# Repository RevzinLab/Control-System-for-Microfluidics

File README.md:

# Control-System-for-Microfluidics

The files included in this repository were developed by The Revzin Lab.

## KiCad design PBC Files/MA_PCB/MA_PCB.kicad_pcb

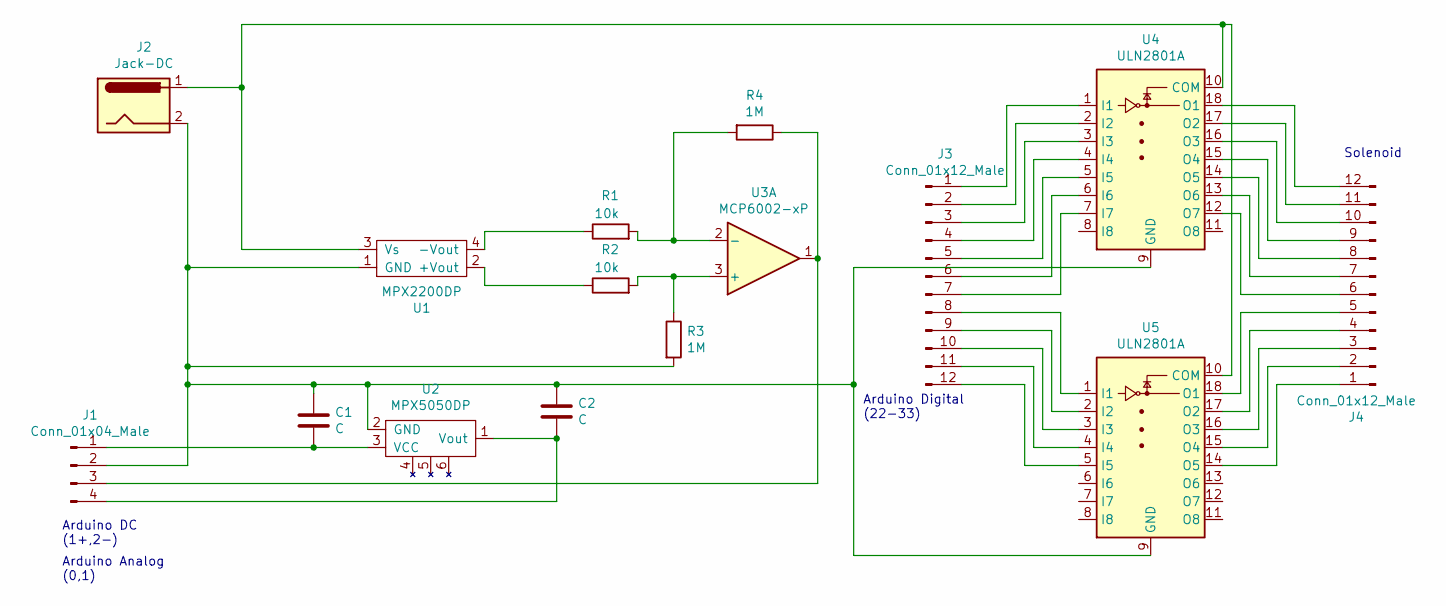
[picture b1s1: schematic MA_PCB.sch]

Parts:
C1, C2: C; CP_Radial_Tantal_D4.5mm_P5.00mm
J1: Conn_01x04_Male; TerminalBlock_4Ucon_1x04_P3.50mm_Vertical
J2: Jack-DC; MI-179PH
J3: Conn_01x12_Male; IDC-Header_2x06-1MP_P2.54mm_Latch6.5mm_Vertical
J4: Conn_01x12_Male; TerminalBlock_4Ucon_1x12_P3.50mm_Vertical
R1, R2: 10k; R_Axial_DIN0207_L6.3mm_D2.5mm_P7.62mm_Horizontal
R3, R4: 1M; R_Axial_DIN0207_L6.3mm_D2.5mm_P7.62mm_Horizontal
U1: MPX2200DP
U2: MPX5050DP
U3: MCP6002-xP; MCP6002
U4, U5: ULN2801A; ULN2803A

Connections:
unnamed: C1.1, C2.1, J1.2, J2.2, R3.2, U1.1 (GND), U2.2 (GND), U4.9 (GND), U5.9 (GND)
unnamed: C1.2, J1.1, U2.3 (VCC)
unnamed: C2.2, J1.4, U2.1 (Vout)
unnamed: J1.3, R4.1, U3.1
unnamed: J2.1, U1.3 (Vs), U4.10 (COM), U5.10 (COM)
unnamed: J3.1, U4.1 (I1)
unnamed: J3.2, U4.2 (I2)
unnamed: J3.3, U4.3 (I3)
unnamed: J3.4, U4.4 (I4)
unnamed: J3.5, U4.5 (I5)
unnamed: J3.6, U4.6 (I6)
unnamed: J3.7, U4.7 (I7)
unnamed: J3.8, U5.1 (I1)
unnamed: J3.9, U5.2 (I2)
unnamed: J3.10, U5.3 (I3)
unnamed: J3.11, U5.4 (I4)
unnamed: J3.12, U5.5 (I5)
unnamed: J4.1, U5.14 (O5)
unnamed: J4.2, U5.15 (O4)
unnamed: J4.3, U5.16 (O3)
unnamed: J4.4, U5.17 (O2)
unnamed: J4.5, U5.18 (O1)
unnamed: J4.6, U4.12 (O7)
unnamed: J4.7, U4.13 (O6)
unnamed: J4.8, U4.14 (O5)
unnamed: J4.9, U4.15 (O4)
unnamed: J4.10, U4.16 (O3)
unnamed: J4.11, U4.17 (O2)
unnamed: J4.12, U4.18 (O1)
unnamed: R1.1, U1.4 (-Vout)
unnamed: R1.2, R4.2, U3.2 (-)
unnamed: R2.1, U1.2 (+Vout)
unnamed: R2.2, R3.1, U3.3 (+)

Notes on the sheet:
Arduino Digital (22-33)
Solenoid
Arduino Analog (0,1)
Arduino DC (1+,2-)

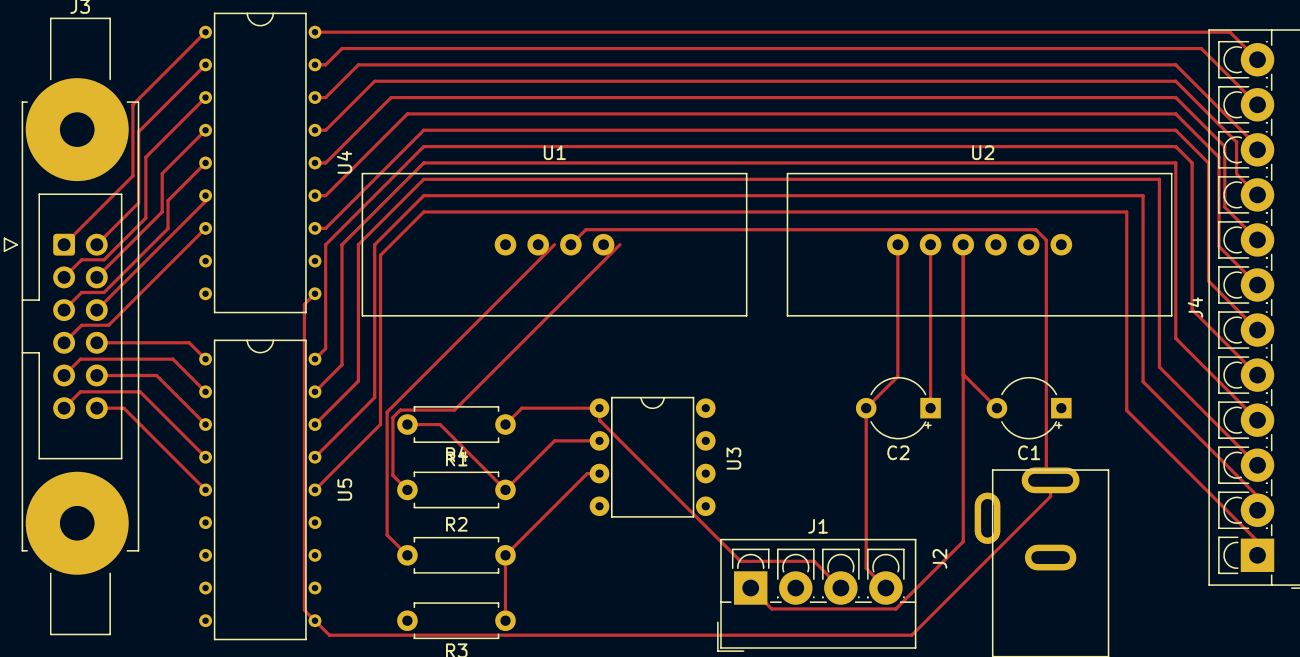
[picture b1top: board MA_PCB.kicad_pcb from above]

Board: 2 copper layers, 15 parts (0 on the bottom side), 33 nets.
